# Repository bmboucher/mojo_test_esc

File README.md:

# mojo_test_esc
Test ESC for Mojo

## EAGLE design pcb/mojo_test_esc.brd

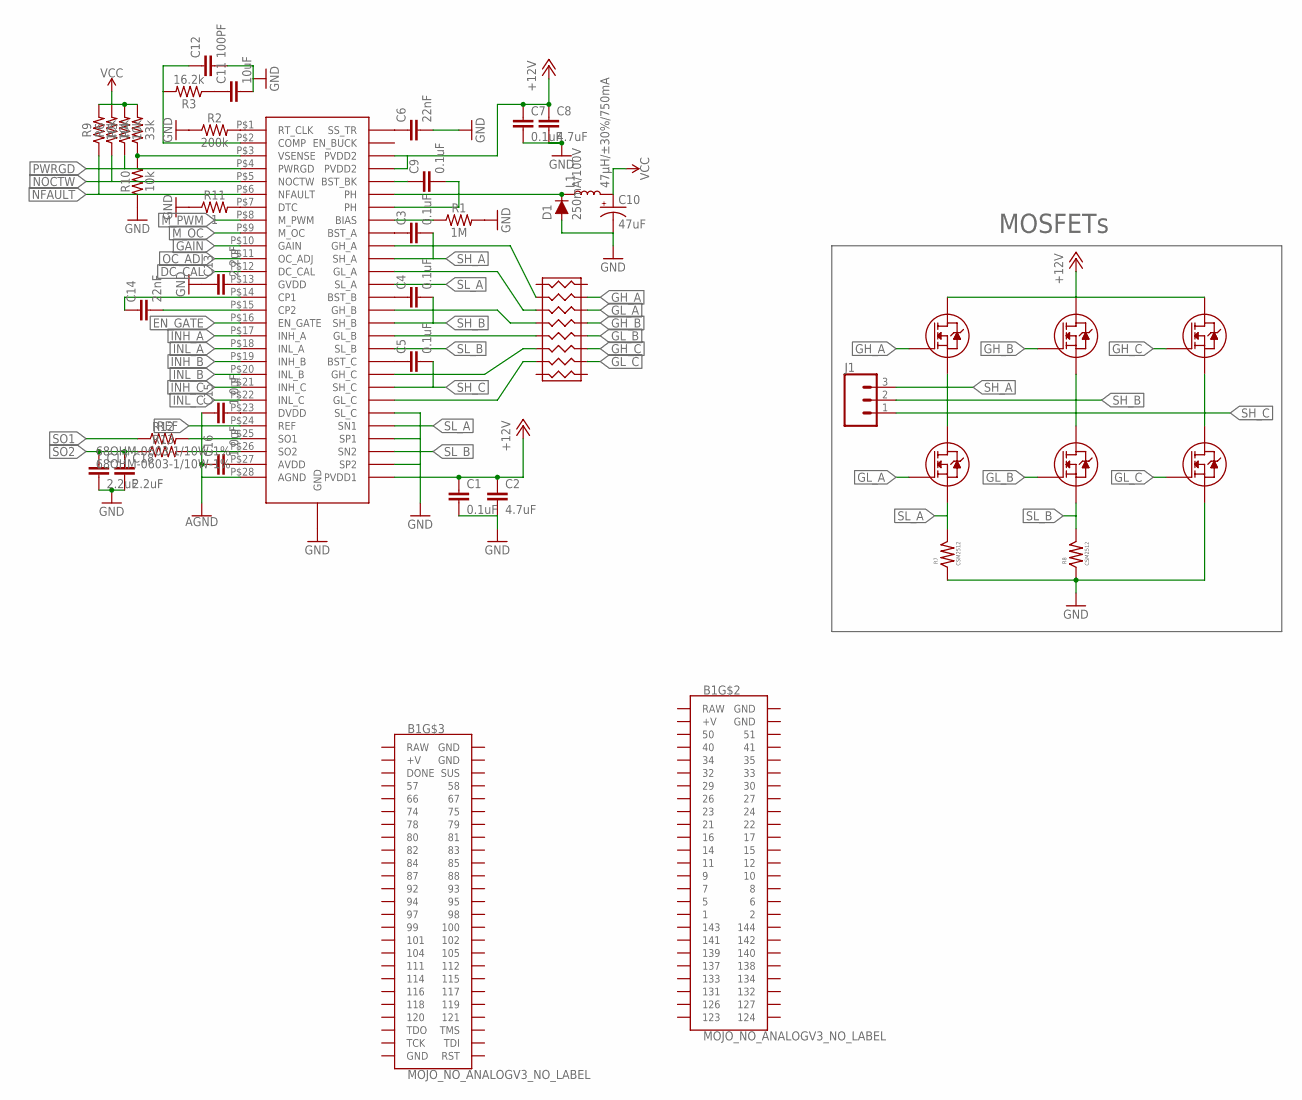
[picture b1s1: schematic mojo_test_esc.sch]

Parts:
B1: MOJO_NO_ANALOGV3_NO_LABEL; MOJO_V3_NO_LABEL_NO_ANALOG
C1, C3, C4, C5, C7, C9: 0.1uF; 0402
C2, C8: 4.7uF; 0603
C6, C14: 22nF; 0603
C10: 47uF; EIA3528
C11: 10uF; 0603
C12: 100PF; 0402
C13, C17, C18: 2.2uF; 0603
C15, C16: 1.0uF; 0402
D1: 250mA/100V; SOD-323
J1: CONN_03-SCREW-5MM; SCREWTERMINAL-5MM-3
L1: 47µH/±30%/750mA; CR54
MOSFET_H_A_1: MOSFET; SOP_ADVANCE
MOSFET_H_B_1: MOSFET; SOP_ADVANCE
MOSFET_H_C_1: MOSFET; SOP_ADVANCE
MOSFET_L_A_1: MOSFET; SOP_ADVANCE
MOSFET_L_B_1: MOSFET; SOP_ADVANCE
MOSFET_L_C_1: MOSFET; SOP_ADVANCE
R1: 1M; 0603
R2: 200k; 0603
R3: 16.2k; 0603
R4: 33k; 0603
R5, R6, R9, R10: 10k; 0603
R7, R8: CSM2512
R11: 1; 0603
R12, R13: 68OHM-0603-1/10W-1%; 0603
U$1: DRV8302
U$2: EXB2HV

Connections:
+12V: C1.1, C2.1, C7.1, C8.1, MOSFET_H_A_1.P$5 (D2), MOSFET_H_A_1.P$6 (D2), MOSFET_H_A_1.P$7 (D2), MOSFET_H_A_1.P$8 (D2), MOSFET_H_A_1.P$9 (D2), MOSFET_H_B_1.P$5 (D2), MOSFET_H_B_1.P$6 (D2), MOSFET_H_B_1.P$7 (D2), MOSFET_H_B_1.P$8 (D2), MOSFET_H_B_1.P$9 (D2), MOSFET_H_C_1.P$5 (D2), MOSFET_H_C_1.P$6 (D2), MOSFET_H_C_1.P$7 (D2), MOSFET_H_C_1.P$8 (D2), MOSFET_H_C_1.P$9 (D2), U$1.P$29 (PVDD1), U$1.P$53 (PVDD2), U$1.P$54 (PVDD2)
AGND: C15.1, C16.1, U$1.P$28 (AGND)
DC_CAL: U$1.P$12 (DC_CAL)
EN_GATE: U$1.P$16 (EN_GATE)
GAIN: U$1.P$10 (GAIN)
GH_A: MOSFET_H_A_1.P$4 (G1)
GH_B: MOSFET_H_B_1.P$4 (G1)
GH_C: MOSFET_H_C_1.P$4 (G1)
GL_A: MOSFET_L_A_1.P$4 (G1)
GL_A_BEF_RES: U$1.P$45 (GL_A), U$2.P3B
GL_B: MOSFET_L_B_1.P$4 (G1)
GL_C: MOSFET_L_C_1.P$4 (G1)
GND: C1.2, C2.2, C6.2, C7.2, C8.2, C10.C (-), C11.2, C12.2, C13.1, C17.2, C18.2, D1.A, MOSFET_L_C_1.P$1 (S3), MOSFET_L_C_1.P$2 (S3), MOSFET_L_C_1.P$3 (S3), R1.2, R2.1, R7.P1L, R7.P2L, R8.P1L, R8.P2L, R10.1, R11.1, U$1.GND_PAD (GND), U$1.GND_PAD2 (GND), U$1.GND_PAD3 (GND), U$1.P$30 (SP2), U$1.P$32 (SP1), U$1.P$34 (SL_C), U$1.VIA1 (GND), U$1.VIA2 (GND), U$1.VIA3 (GND), U$1.VIA4 (GND), U$1.VIA5 (GND), U$1.VIA6 (GND), U$1.VIA7 (GND), U$1.VIA8 (GND), U$1.VIA9 (GND), U$1.VIA10 (GND), U$1.VIA11 (GND), U$1.VIA12 (GND), U$1.VIA13 (GND), U$1.VIA14 (GND), U$1.VIA15 (GND), U$1.VIA16 (GND), U$1.VIA17 (GND), U$1.VIA18 (GND), U$1.VIA19 (GND), U$1.VIA20 (GND), U$1.VIA21 (GND), U$1.VIA22 (GND), U$1.VIA23 (GND), U$1.VIA24 (GND), U$1.VIA25 (GND), U$1.VIA26 (GND), U$1.VIA27 (GND), U$1.VIA28 (GND), U$1.VIA29 (GND), U$1.VIA30 (GND), U$1.VIA31 (GND), U$1.VIA32 (GND), U$1.VIA33 (GND), U$1.VIA34 (GND), U$1.VIA35 (GND), U$1.VIA36 (GND), U$1.VIA37 (GND), U$1.VIA38 (GND), U$1.VIA39 (GND), U$1.VIA40 (GND), U$1.VIA41 (GND), U$1.VIA42 (GND), U$1.VIA43 (GND), U$1.VIA44 (GND)
INH_A: U$1.P$17 (INH_A)
INH_B: U$1.P$19 (INH_B)
INH_C: U$1.P$21 (INH_C)
INL_A: U$1.P$18 (INL_A)
INL_B: U$1.P$20 (INL_B)
INL_C: U$1.P$22 (INL_C)
M_OC: U$1.P$9 (M_OC)
M_PWM: U$1.P$8 (M_PWM)
unnamed: U$1.P$47 (GH_A), U$2.P2B
unnamed: C6.1, U$1.P$56 (SS_TR)
unnamed: U$1.P$42 (GH_B), U$2.P4B
unnamed: U$1.P$40 (GL_B), U$2.P5B
unnamed: U$1.P$37 (GH_C), U$2.P6B
unnamed: U$1.P$35 (GL_C), U$2.P7B
unnamed: C3.1, U$1.P$48 (BST_A)
unnamed: C4.1, U$1.P$43 (BST_B)
unnamed: C5.1, U$1.P$38 (BST_C)
unnamed: C9.1, U$1.P$52 (BST_BK)
unnamed: C9.2, D1.C, L1.P$1 (1), U$1.P$50 (PH), U$1.P$51 (PH)
unnamed: R2.2, U$1.P$1 (RT_CLK)
unnamed: R1.1, U$1.P$49 (BIAS)
unnamed: C12.1, R3.2, U$1.P$2 (COMP)
unnamed: C11.1, R3.1
unnamed: R11.2, U$1.P$7 (DTC)
unnamed: C13.2, U$1.P$13 (GVDD)
unnamed: C14.1, U$1.P$14 (CP1)
unnamed: R4.1, R10.2, U$1.P$3 (VSENSE)
unnamed: C14.2, U$1.P$15 (CP2)
unnamed: C15.2, U$1.P$23 (DVDD)
unnamed: C16.2, U$1.P$27 (AVDD)
unnamed: R12.2, U$1.P$25 (SO1)
unnamed: R13.2, U$1.P$26 (SO2)
NFAULT: R9.1, U$1.P$6 (NFAULT)
NOCTW: R6.1, U$1.P$5 (NOCTW)
OC_ADJ: U$1.P$11 (OC_ADJ)
PWRGD: R5.1, U$1.P$4 (PWRGD)
REF: U$1.P$24 (REF)
SH_A: C3.2, J1.3, MOSFET_H_A_1.P$1 (S3), MOSFET_H_A_1.P$2 (S3), MOSFET_H_A_1.P$3 (S3), MOSFET_L_A_1.P$5 (D2), MOSFET_L_A_1.P$6 (D2), MOSFET_L_A_1.P$7 (D2), MOSFET_L_A_1.P$8 (D2), MOSFET_L_A_1.P$9 (D2), U$1.P$46 (SH_A)
SH_B: C4.2, J1.2, MOSFET_H_B_1.P$1 (S3), MOSFET_H_B_1.P$2 (S3), MOSFET_H_B_1.P$3 (S3), MOSFET_L_B_1.P$5 (D2), MOSFET_L_B_1.P$6 (D2), MOSFET_L_B_1.P$7 (D2), MOSFET_L_B_1.P$8 (D2), MOSFET_L_B_1.P$9 (D2), U$1.P$41 (SH_B)
SH_C: C5.2, J1.1, MOSFET_H_C_1.P$1 (S3), MOSFET_H_C_1.P$2 (S3), MOSFET_H_C_1.P$3 (S3), MOSFET_L_C_1.P$5 (D2), MOSFET_L_C_1.P$6 (D2), MOSFET_L_C_1.P$7 (D2), MOSFET_L_C_1.P$8 (D2), MOSFET_L_C_1.P$9 (D2), U$1.P$36 (SH_C)
SL_A: MOSFET_L_A_1.P$1 (S3), MOSFET_L_A_1.P$2 (S3), MOSFET_L_A_1.P$3 (S3), R7.P1R, R7.P2R, U$1.P$33 (SN1), U$1.P$44 (SL_A)
SL_B: MOSFET_L_B_1.P$1 (S3), MOSFET_L_B_1.P$2 (S3), MOSFET_L_B_1.P$3 (S3), R8.P1R, R8.P2R, U$1.P$31 (SN2), U$1.P$39 (SL_B)
SO1: R12.1
SO2: C17.1, C18.1, R13.1
VCC: C10.A (+), L1.P$2 (2), R4.2, R5.2, R6.2, R9.2

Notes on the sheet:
MOSFETs

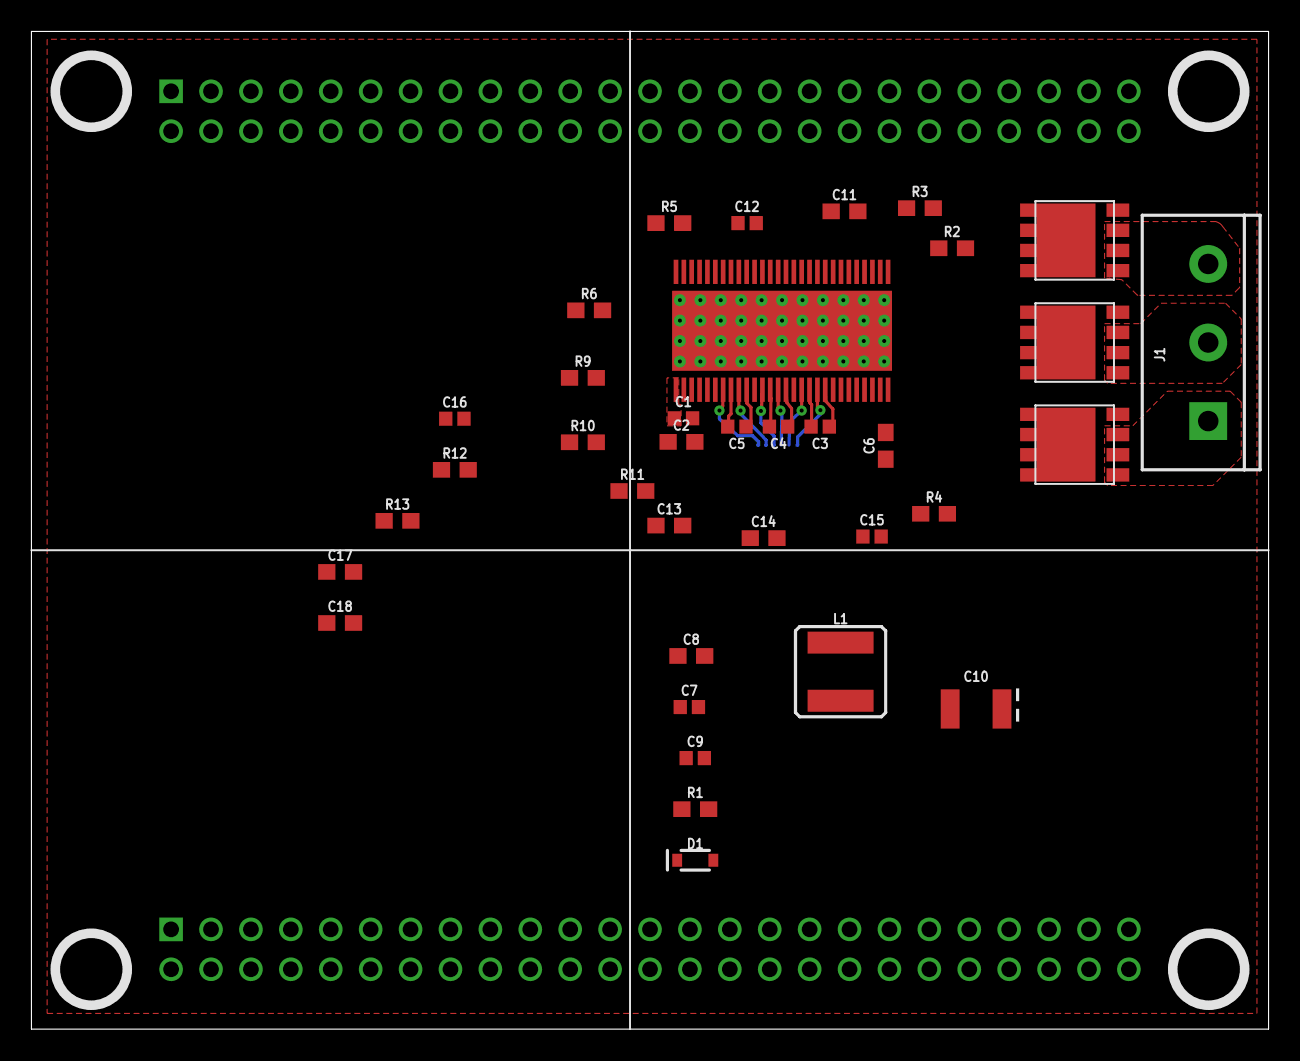
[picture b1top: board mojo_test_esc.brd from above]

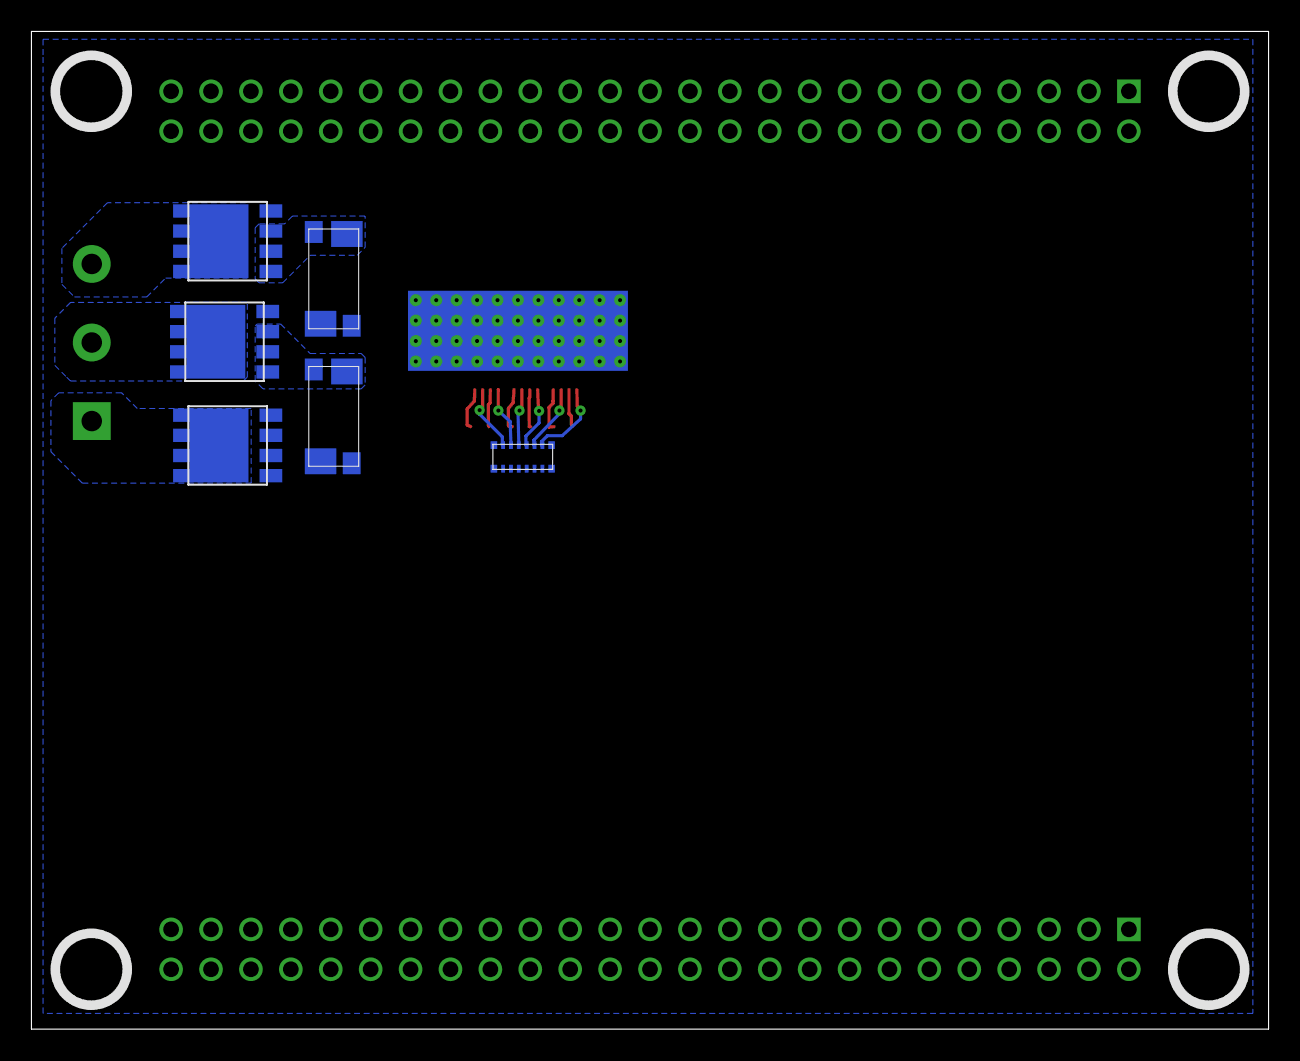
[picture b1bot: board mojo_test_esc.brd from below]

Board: 2 copper layers, 78.7 x 63.5 mm, 43 parts (6 on the bottom side), 38 nets.

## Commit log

2017-10-09 Initial commit - pcb subfolder
2017-10-09 Updating LICENSE
2017-10-09 Adding mojo_test_esc.lbr with Mojo pinout
2017-10-09 Creating basic board layout/schematic from Mojo pinout
2017-10-09 Adding DRV8302 to mojo_test_esc library
2017-10-09 Adding datasheet for DRV8302
2017-10-09 Adding D2PAK mosfet to library
2017-10-09 Adding SOT23 mosfet packages and associated datasheet
2017-10-09 Adding 8-pack resistor and updating MOSFETs again
2017-10-09 Initial layout with capacitors

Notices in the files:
parts and their libraries:
SparkFun-Connectors: Licensing: Creative Commons ShareAlike 4.0 International - https://creativecommons.org/licenses/by-sa/4.0
